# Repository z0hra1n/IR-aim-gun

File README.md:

This is a gun peripheral for fps games with a recoil mechanism and tactile reload and a joystick for movement inspired by the wii remote.

I made this project because it has been going in my head for a while i just wondered why has no one made it yet.I did want to make it before but i didnt have the funding now with stasis, im making it real.The recoil mechanism was inspired by my little brother's toy gun.

## Bill of Materials

| Purpose                                   | Component / Item                     | Qty | Total Cost (USD) | Distributor | Link |
|-------------------------------------------|-------------------------------------|-----|------------------|------------|------|
| Solenoid driver control                   | PCB (JLCPCB)                        | 1   | 2.10             | JLCPCB     | https://cart.jlcpcb.com/quote?rand=0.9395806180197926 |
| Solenoid driver board                     | Driver Module                       | 1   | 0.39             | Robu.in    | https://robu.in/product/1-month-warranty-1004/ |
| Solenoid driver board                     | 10kΩ SMD Resistors (0805, pack)     | 10  | 0.02             | Robu.in    | https://robu.in/product/10k-ohm-1-4w-0805-surface-mount-chip-resistor-pack-of-10/ |
| Solenoid driver board                     | 220Ω SMD Resistors (0805, pack)     | 10  | 0.04             | Robu.in    | https://robu.in/product/rc0805fr-07220rlyageores-smd-220-ohm-5-1-2w-0805/ |
| Main casing                               | 3D Printing Service                 | 1   | 6.63             | Robu.in    | https://robu.in/product/3d-printing-service/ |
| Solenoid driving                          | IRLZ44N MOSFET                      | 1   | 0.42             | Robu.in    | https://robu.in/product/irlz44n/ |
| Recoil mechanism                          | Push-Pull Solenoid                  | 1   | 5.90             | Amazon     | https://www.amazon.in/xcluma-JF-0826B-Push-Pull-Solenoid-Electromagnet/dp/B09XK2MBQP/ |
| Power supply                              | 1500mAh Li-Po Battery               | 1   | 3.00             | Robu.in    | https://robu.in/product/1500mah-pcm-protected-micro-li-po-battery/ |
| Voltage stabilization                     | 1000µF Capacitor                    | 1   | 0.12             | Robu.in    | https://robu.in/product/1000uf-25v-electrolytic-capacitor-dip-pack-of-5/ |
| Voltage conversion                        | 3.7V to 5V Boost Converter          | 1   | 0.85             | Robu.in    | https://robu.in/product/3-7v-to-9v-5v-2a-multimeter-modified-charger-boost/ |
| User input (trigger & reload)             | Push Button Switches                | 5   | 1.05             | Robu.in    | https://robu.in/product/red-r13-507-16mm-no-lock-push-button-momentary-switch-3a-250v/ |
| IR emission                               | IR LED Emitter Module               | 1   | 3.43             | Amazon     | https://www.amazon.in/Invento-Emitter-Transmitter-Infrared-Projects/dp/B07GD1JDR6/ |
| Cursor positioning                        | IR Positioning Camera (DFRobot)     | 1   | 23.90            | Robu.in    | https://robu.in/product/dfrobot-gravity-ir-positioning-camera-for-arduino/ |
| For movement in games.                    | Joystick module                     | 1   | 0.39             | Robu.in    |https://robu.in/product/joystick-module-ps2-breakout-sensor/ |

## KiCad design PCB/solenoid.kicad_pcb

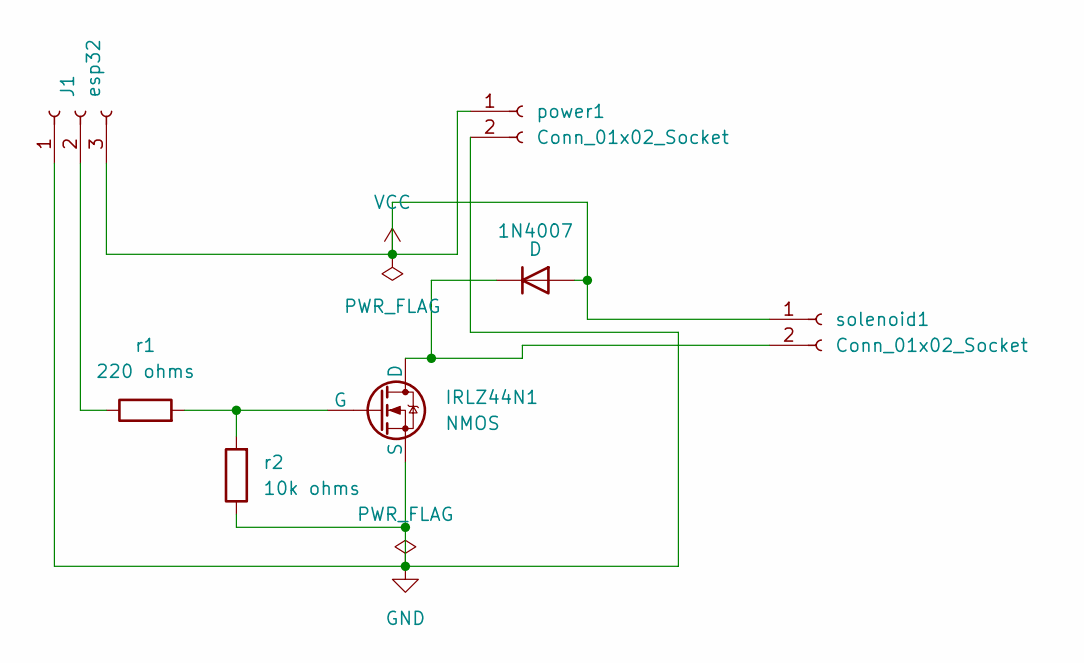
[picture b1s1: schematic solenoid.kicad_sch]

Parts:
1N4007: D; D_SMA; LCSC Part # C20754788
IRLZ44N1: NMOS; TO-220-3_Vertical
J1: esp32; PinHeader_1x03_P2.54mm_Vertical
power1: Conn_01x02_Socket; PinSocket_1x02_P2.54mm_Vertical
r1: 220 ohms; R_0805_2012Metric; LCSC Part # C17557
r2: 10k ohms; R_0805_2012Metric; LCSC Part # C84376
solenoid1: Conn_01x02_Socket; PinSocket_1x02_P2.54mm_Vertical

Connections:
GND: IRLZ44N1.3 (S), J1.1, power1.2, r2.1
unnamed: 1N4007.1 (K), IRLZ44N1.1 (D), solenoid1.2
unnamed: IRLZ44N1.2 (G), r1.2, r2.2
unnamed: J1.2, r1.1
VCC: 1N4007.2 (A), J1.3, power1.1, solenoid1.1

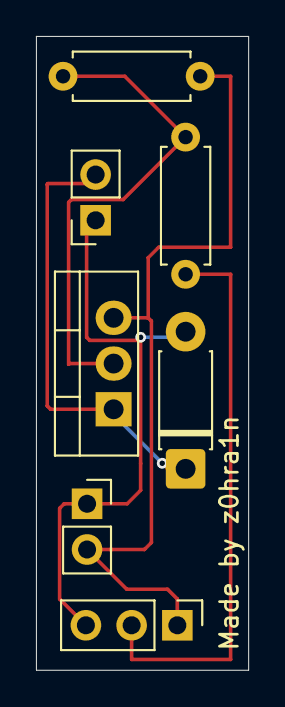
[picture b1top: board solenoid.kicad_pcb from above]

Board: 2 copper layers, 11.8 x 35.2 mm, 7 parts (0 on the bottom side), 5 nets.

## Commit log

2026-03-23 README with project details and images
    Added project description and images for a gun peripheral.
2026-03-23 Add Bill of Materials to README
    Added a Bill of Materials section with components, quantities, costs, and links.
2026-03-23 Create lol
2026-03-23 Added the firmware.
2026-03-27 Rename IR aim gun-bom (1).csv to IR aim gun-bom.csv
